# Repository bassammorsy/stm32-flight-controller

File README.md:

# STM32F405 Quadcopter Flight Controller
A custom 4-layer flight controller PCB designed from scratch in KiCad, targeting Betaflight compatibility with 4S–6S LiPo input. Designed, laid out, and submitted for SMT assembly through JLCPCB.

## Specifications
| Parameter | Detail |
|---|---|
| Microcontroller | STM32F405RGTx — ARM Cortex-M4 @ 168 MHz |
| Input Voltage | 4S–6S LiPo (14.8V–25.2V) |
| Power Architecture | TPS54360DDA Buck (5V/3.5A) → SPX3819 LDO (3.3V) |
| IMU | ICM-42688-P (SPI1, 6-DOF, 32kHz ODR) |
| Barometer | BMP388 (SPI3) |
| Magnetometer | QMC5883L (I2C2) |
| GPS | SAM-M10Q-00B (UART3, integrated antenna) |
| OSD | AT7456E with 27MHz crystal |
| USB | USB-C with USBLC6-2SC6 ESD protection |
| PCB | 4-Layer, 74×108mm, FR4 TG135, LeadFree HASL |
| Motor Outputs | 4× DShot (TIM1 CH1-3, TIM8 CH4) |
| Assembly | JLCPCB SMT — 43 component BOM |

## PCB Layout

## Design Portfolio
A full design portfolio documenting every schematic section, PCB layout decision, component selection rationale, and datasheet calculations is available below.

[📄 View Full Design Portfolio (PDF)](Docs/STM32_Drone_FC_Portfolio.pdf)

## Key Design Decisions
- 4-layer stackup: F.Cu (signals) / In1.Cu (GND plane) / In2.Cu (signal overflow) / B.Cu (3.3V distribution)
- Switched node area minimized around TPS54360 to reduce EMI
- Decoupling capacitors placed within 1–2mm of every power pin
- Ground via stitching at all signal layer transitions
- Magnetometer placed at maximum distance from power section
- USBLC6-2SC6 placed immediately at USB-C connector before any D+/D− routing

## Repository Structure

    Hardware/
        Schematic/     — KiCad schematic files
        PCB/           — KiCad PCB layout files
        Gerbers/       — Fabrication files for JLCPCB
    BOM/               — Bill of materials with LCSC part numbers
    Docs/              — Full design portfolio PDF

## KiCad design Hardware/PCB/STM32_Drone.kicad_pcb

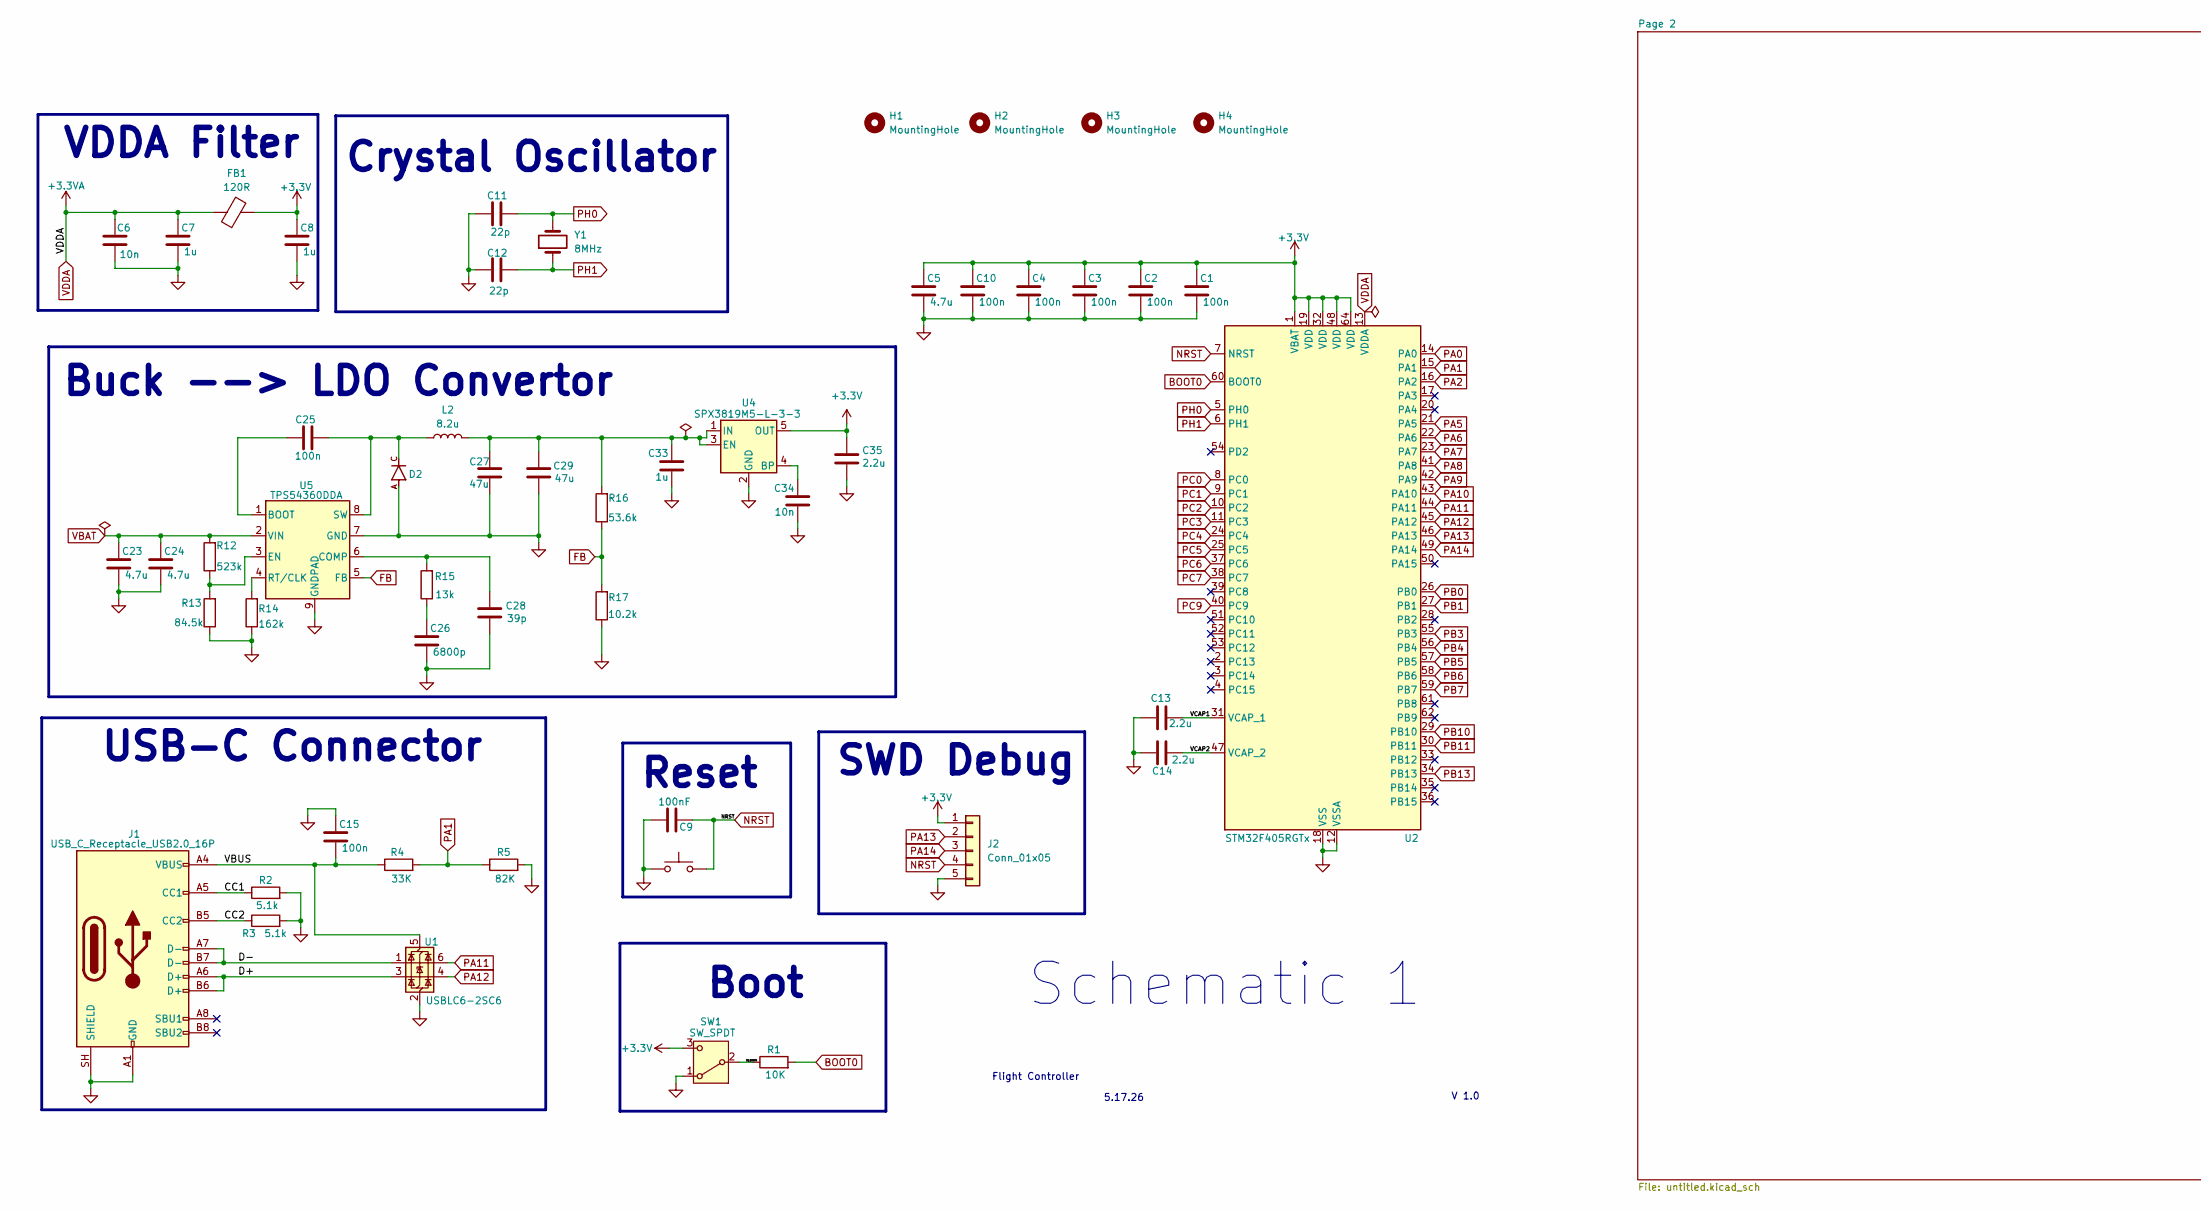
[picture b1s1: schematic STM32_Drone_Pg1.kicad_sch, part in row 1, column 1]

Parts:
C1, C2, C3, C4, C10, C15, C25: 100n; C_0402_1005Metric
C5: 4.7u; C_0805_2012Metric
C6, C34: 10n; C_0402_1005Metric
C7, C8: 1u; C_0805_2012Metric
C9: 100nF; C_0402_1005Metric
C11, C12: 22p; C_0402_1005Metric
C13, C14, C35: 2.2u; C_0402_1005Metric
C23, C24: 4.7u; C_1210_3225Metric
C26: 6800p; C_0402_1005Metric
C27, C29: 47u; C_1210_3225Metric
C28: 39p; C_0402_1005Metric
C33: 1u; C_0402_1005Metric
D2: B560C-13-F; B560C-13F
FB1: 120R; L_0402_1005Metric
H1, H2, H3, H4: MountingHole; MountingHole_3.2mm_M3
J1: USB_C_Receptacle_USB2.0_16P; USB_C_Receptacle_XKB_U262-16XN-4BVC11
J2: Conn_01x05; PinHeader_1x05_P2.54mm_Vertical
L2: 8.2u; L_7.3x7.3_H3.5
R1: 10K; R_0402_1005Metric
R2, R3: 5.1k; R_0402_1005Metric
R4: 33K; R_0402_1005Metric
R5: 82K; R_0402_1005Metric
R12: 523k; R_0402_1005Metric
R13: 84.5k; R_0402_1005Metric
R14: 162k; R_0402_1005Metric
R15: 13k; R_0402_1005Metric
R16: 53.6k; R_0402_1005Metric
R17: 10.2k; R_0402_1005Metric
SW1: SW_SPDT; SW_SPDT_CK_JS102011SAQN
SW2: SW_Push; SW_Push_1P1T_XKB_TS-1187A
U1: USBLC6-2SC6; SOT-23-6
U2: STM32F405RGTx; LQFP-64_10x10mm_P0.5mm
U4: SPX3819M5-L-3-3; SOT-23-5
U5: TPS54360DDA; TI_SO-PowerPAD-8_ThermalVias
Y1: 8MHz; Crystal_SMD_3225-4Pin_3.2x2.5mm

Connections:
+3.3V: C1.2, C2.2, C3.2, C4.2, C5.2, C8.2, C10.2, C35.1, FB1.2, J2.1, SW1.3 (C), U2.1 (VBAT), U2.19 (VDD), U2.32 (VDD), U2.48 (VDD), U2.64 (VDD), U4.5 (OUT); also elsewhere on the board
/CC1: J1.A5 (CC1), R2.1
/CC2: J1.B5 (CC2), R3.1
/D+: J1.A6 (D+), J1.B6 (D+), U1.3 (I/O2)
/D-: J1.A7 (D-), J1.B7 (D-), U1.1 (I/O1)
/SW_BOOT0: R1.1, SW1.2 (B)
/VBUS: C15.1, J1.A4 (VBUS), J1.A9 (VBUS), J1.B4 (VBUS), J1.B9 (VBUS), R4.1, U1.5 (VBUS)
/VCAP1: C13.1, U2.31 (VCAP_1)
/VCAP2: C14.1, U2.47 (VCAP_2)
BOOT0: R1.2, U2.60 (BOOT0)
FB: R16.1, R17.2, U5.5 (FB)
GND: C1.1, C2.1, C3.1, C4.1, C5.1, C6.1, C7.1, C8.1, C9.1, C10.1, C11.2, C12.2, C13.2, C14.2, C15.2, C23.1, C24.1, C26.1, C27.1, C28.1, C29.1, C33.2, C34.2, C35.2, D2.A, J1.A1 (GND), J1.A12 (GND), J1.B1 (GND), J1.B12 (GND), J1.SH (SHIELD), J2.5, R2.2, R3.2, R5.2, R13.1, R14.1, R17.1, SW1.1 (A), SW2.1, U1.2 (GND), U2.12 (VSSA), U2.18 (VSS), U2.63 (VSS), U4.2 (GND), U5.7 (GND), U5.9 (GNDPAD); also elsewhere on the board
NRST: C9.2, J2.4, SW2.2, U2.7 (NRST)
unnamed: C26.2, R15.1
unnamed: C34.1, U4.4 (BP)
unnamed: C27.2, C29.2, C33.1, L2.2, R16.2, U4.1 (IN), U4.3 (EN)
unnamed: C25.2, U5.1 (BOOT)
unnamed: C28.2, R15.2, U5.6 (COMP)
unnamed: R12.1, R13.2, U5.3 (EN)
unnamed: R14.2, U5.4 (RT/CLK)
unnamed: C25.1, D2.C, L2.1, U5.8 (SW)
PA0: U2.14 (PA0); also elsewhere on the board
PA1: R4.2, R5.1, U2.15 (PA1)
PA2: U2.16 (PA2); also elsewhere on the board
PA5: U2.21 (PA5); also elsewhere on the board
PA6: U2.22 (PA6); also elsewhere on the board
PA7: U2.23 (PA7); also elsewhere on the board
PA8: U2.41 (PA8); also elsewhere on the board
PA9: U2.42 (PA9); also elsewhere on the board
PA10: U2.43 (PA10); also elsewhere on the board
PA11: U1.6 (I/O1), U2.44 (PA11)
PA12: U1.4 (I/O2), U2.45 (PA12)
PA13: J2.2, U2.46 (PA13)
PA14: J2.3, U2.49 (PA14)
PB0: U2.26 (PB0); also elsewhere on the board
PB1: U2.27 (PB1); also elsewhere on the board
PB3: U2.55 (PB3); also elsewhere on the board
PB4: U2.56 (PB4); also elsewhere on the board
PB5: U2.57 (PB5); also elsewhere on the board
PB6: U2.58 (PB6); also elsewhere on the board
PB7: U2.59 (PB7); also elsewhere on the board
PB10: U2.29 (PB10); also elsewhere on the board
PB11: U2.30 (PB11); also elsewhere on the board
PB13: U2.34 (PB13); also elsewhere on the board
PC0: U2.8 (PC0); also elsewhere on the board
PC1: U2.9 (PC1); also elsewhere on the board
PC2: U2.10 (PC2); also elsewhere on the board
PC3: U2.11 (PC3); also elsewhere on the board
PC4: U2.24 (PC4); also elsewhere on the board
PC5: U2.25 (PC5); also elsewhere on the board
PC6: U2.37 (PC6); also elsewhere on the board
PC7: U2.38 (PC7); also elsewhere on the board
PC9: U2.40 (PC9); also elsewhere on the board
PH0: C11.1, U2.5 (PH0), Y1.2
PH1: C12.1, U2.6 (PH1), Y1.1
VBAT: C23.2, C24.2, R12.2, U5.2 (VIN); also elsewhere on the board
VDDA: C6.2, C7.2, FB1.1, U2.13 (VDDA)

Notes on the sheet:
V 1.0
SWD Debug
5.17.26
Boot
Reset
Schematic 1
Flight Controller
VDDA Filter
Buck --> LDO Convertor
Crystal Oscillator
USB-C Connector

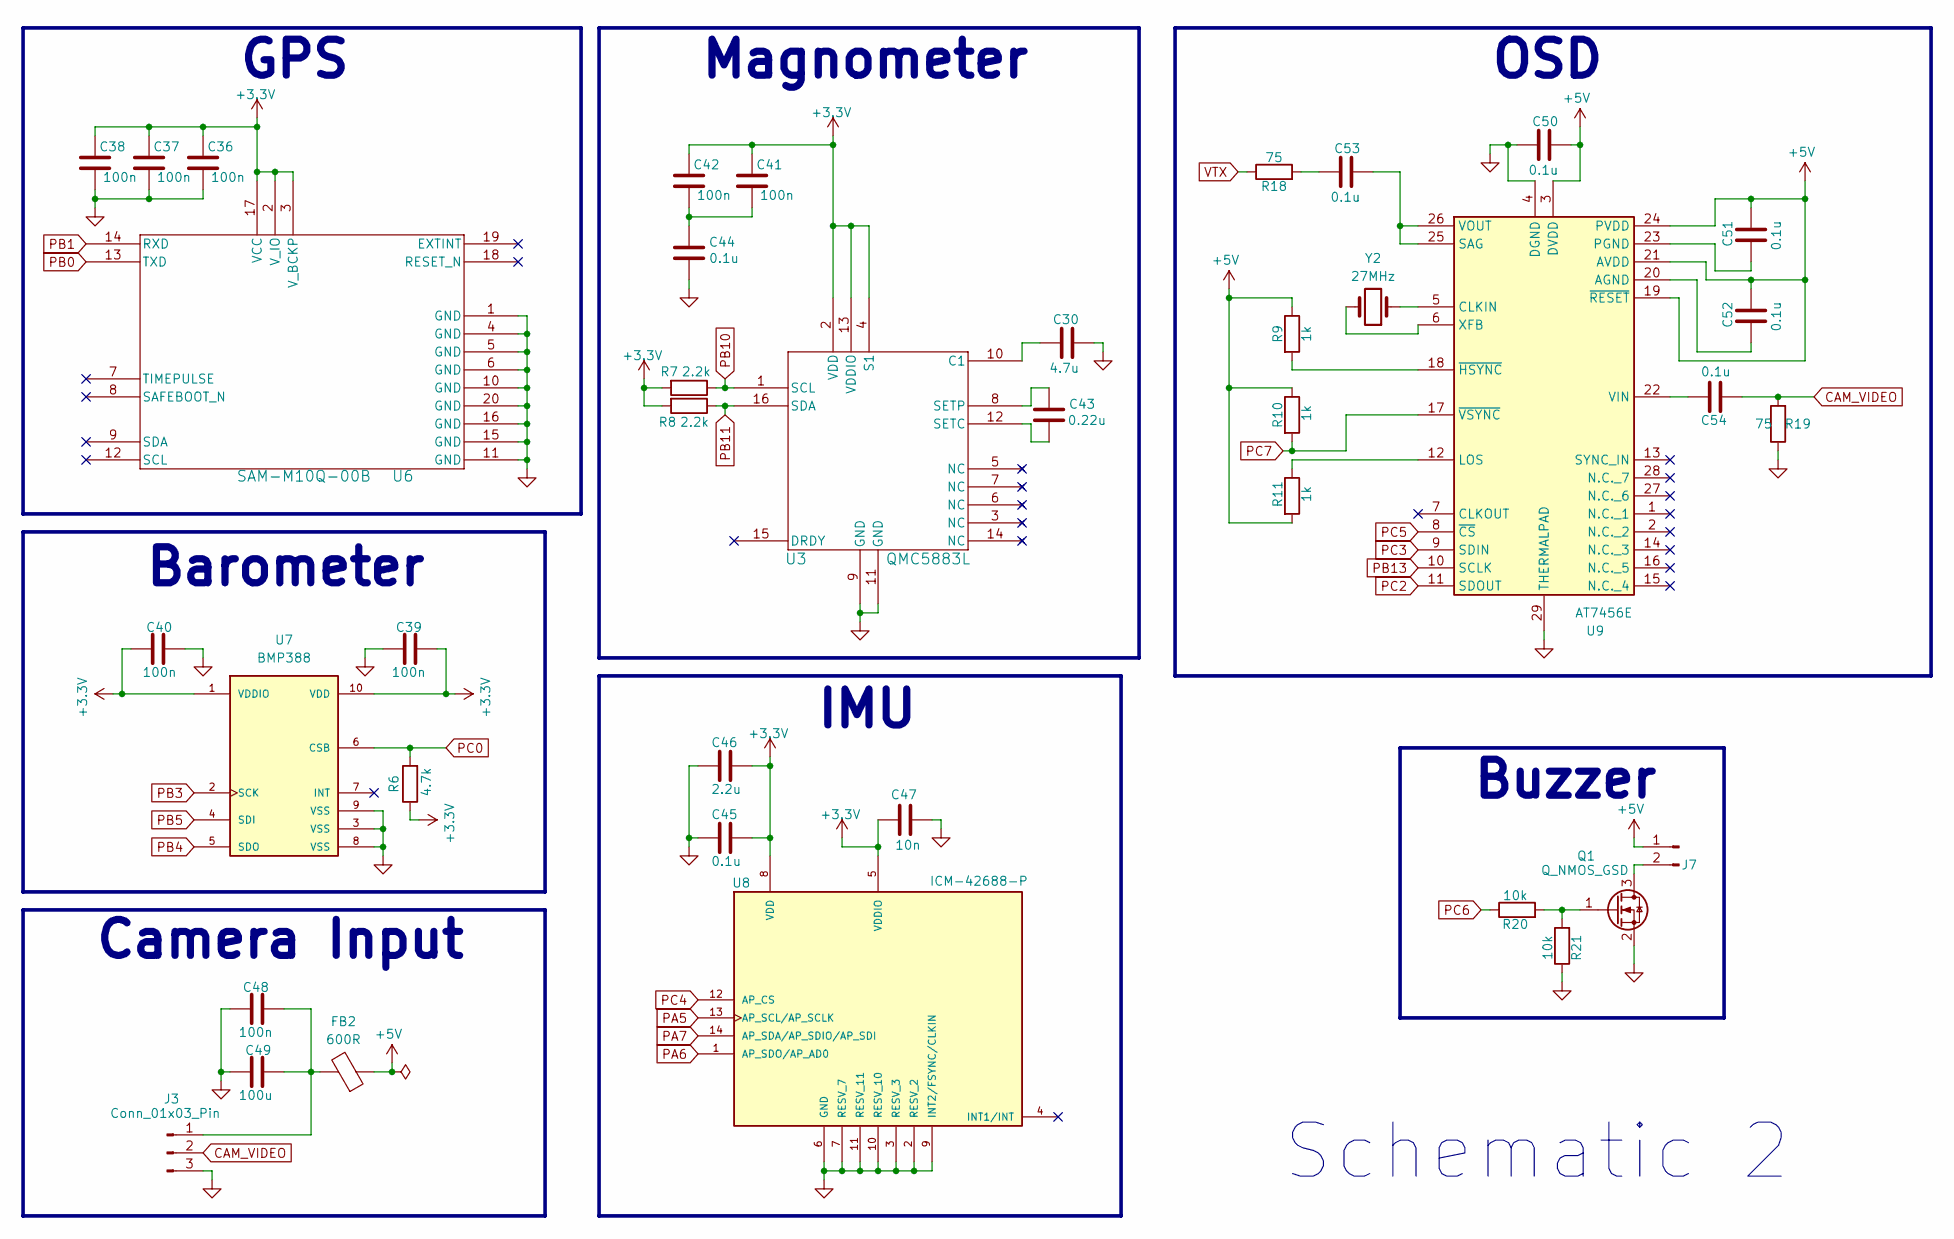
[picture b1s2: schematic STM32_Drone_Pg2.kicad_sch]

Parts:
C30: 4.7u; C_1210_3225Metric
C36, C37, C38, C39, C40, C41, C42, C48: 100n; C_0402_1005Metric
C43: 0.22u; C_0402_1005Metric
C44, C45, C50, C51, C52, C53, C54: 0.1u; C_0402_1005Metric
C46: 2.2u; C_0402_1005Metric
C47: 10n; C_0402_1005Metric
C49: 100u; C_1206_3216Metric
FB2: 600R; L_0402_1005Metric
J3: Conn_01x03_Pin; JST_SH_BM03B-SRSS-TB_1x03-1MP_P1.00mm_Vertical
J7: Conn_01x02_Pin; JST_SH_BM02B-SRSS-TB_1x02-1MP_P1.00mm_Vertical
Q1: Q_NMOS_GSD; SOT-23
R6: 4.7k; R_0402_1005Metric
R7, R8: 2.2k; R_0402_1005Metric
R9, R10, R11: 1k; R_0402_1005Metric
R18, R19: 75; R_0402_1005Metric
R20, R21: 10k; R_0402_1005Metric
U3: QMC5883L; LPCC-16
U6: SAM-M10Q-00B; XCVR_SAM-M10Q-00B
U7: BMP388; XDCR_BMP388; PARTREV 1.7
U8: ICM-42688-P; PQFN50P300X250X97-14N; PARTREV 1.2
U9: AT7456E; SOP65P640X120-29N; Manufacturer_Part_Number AT7456E
Y2: 27MHz; Crystal_SMD_3225-4Pin_3.2x2.5mm

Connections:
+3.3V: C36.2, C37.2, C38.2, C39.1, C40.1, C41.2, C42.2, C45.2, C46.2, C47.2, R6.1, R7.2, R8.2, U3.2 (VDD), U3.4 (S1), U3.13 (VDDIO), U6.2 (V_IO), U6.3 (V_BCKP), U6.17 (VCC), U7.1 (VDDIO), U7.10 (VDD), U8.5 (VDDIO), U8.8 (VDD); also elsewhere on the board
+5V: C50.2, C51.2, C52.2, FB2.1, J7.1, R9.1, R10.1, R11.2, U9.3 (DVDD), U9.19 (~RESET), U9.21 (AVDD), U9.24 (PVDD); also elsewhere on the board
CAM_VIDEO: C54.1, J3.2, R19.2
GND: C30.1, C36.1, C37.1, C38.1, C39.2, C40.2, C44.2, C45.1, C46.1, C47.1, C48.2, C49.2, C50.1, J3.3, Q1.2 (S), R19.1, R21.1, U3.9 (GND), U3.11 (GND), U6.1 (GND), U6.4 (GND), U6.5 (GND), U6.6 (GND), U6.10 (GND), U6.11 (GND), U6.15 (GND), U6.16 (GND), U6.20 (GND), U7.3 (VSS), U7.8 (VSS), U7.9 (VSS), U8.2 (RESV_2), U8.3 (RESV_3), U8.6 (GND), U8.7 (RESV_7), U8.9 (INT2/FSYNC/CLKIN), U8.10 (RESV_10), U8.11 (RESV_11), U9.4 (DGND), U9.29 (THERMALPAD); also elsewhere on the board
unnamed: C41.1, C42.1, C44.1
unnamed: C53.1, R18.2
unnamed: C48.1, C49.1, FB2.2, J3.1
unnamed: J7.2, Q1.3 (D)
unnamed: Q1.1 (G), R20.2, R21.2
unnamed: C30.2, U3.10 (C1)
unnamed: C43.2, U3.12 (SETC)
unnamed: C43.1, U3.8 (SETP)
unnamed: C52.1, U9.20 (AGND)
unnamed: U9.5 (CLKIN), Y2.1
unnamed: R11.1, U9.12 (LOS)
unnamed: C51.1, U9.23 (PGND)
unnamed: C53.2, U9.25 (SAG), U9.26 (VOUT)
unnamed: C54.2, U9.22 (VIN)
unnamed: U9.6 (XFB), Y2.2
unnamed: R9.2, U9.18 (~HSYNC)
PA5: U8.13 (AP_SCL/AP_SCLK); also elsewhere on the board
PA6: U8.1 (AP_SDO/AP_AD0); also elsewhere on the board
PA7: U8.14 (AP_SDA/AP_SDIO/AP_SDI); also elsewhere on the board
PB0: U6.13 (TXD); also elsewhere on the board
PB1: U6.14 (RXD); also elsewhere on the board
PB3: U7.2 (SCK); also elsewhere on the board
PB4: U7.5 (SDO); also elsewhere on the board
PB5: U7.4 (SDI); also elsewhere on the board
PB10: R7.1, U3.1 (SCL); also elsewhere on the board
PB11: R8.1, U3.16 (SDA); also elsewhere on the board
PB13: U9.10 (SCLK); also elsewhere on the board
PC0: R6.2, U7.6 (CSB); also elsewhere on the board
PC2: U9.11 (SDOUT); also elsewhere on the board
PC3: U9.9 (SDIN); also elsewhere on the board
PC4: U8.12 (AP_CS); also elsewhere on the board
PC5: U9.8 (~CS); also elsewhere on the board
PC6: R20.1; also elsewhere on the board
PC7: R10.2, U9.17 (~VSYNC); also elsewhere on the board
VTX: R18.1; also elsewhere on the board

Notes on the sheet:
OSD
Barometer
Schematic 2
Buzzer
Magnometer
IMU
GPS
Camera Input

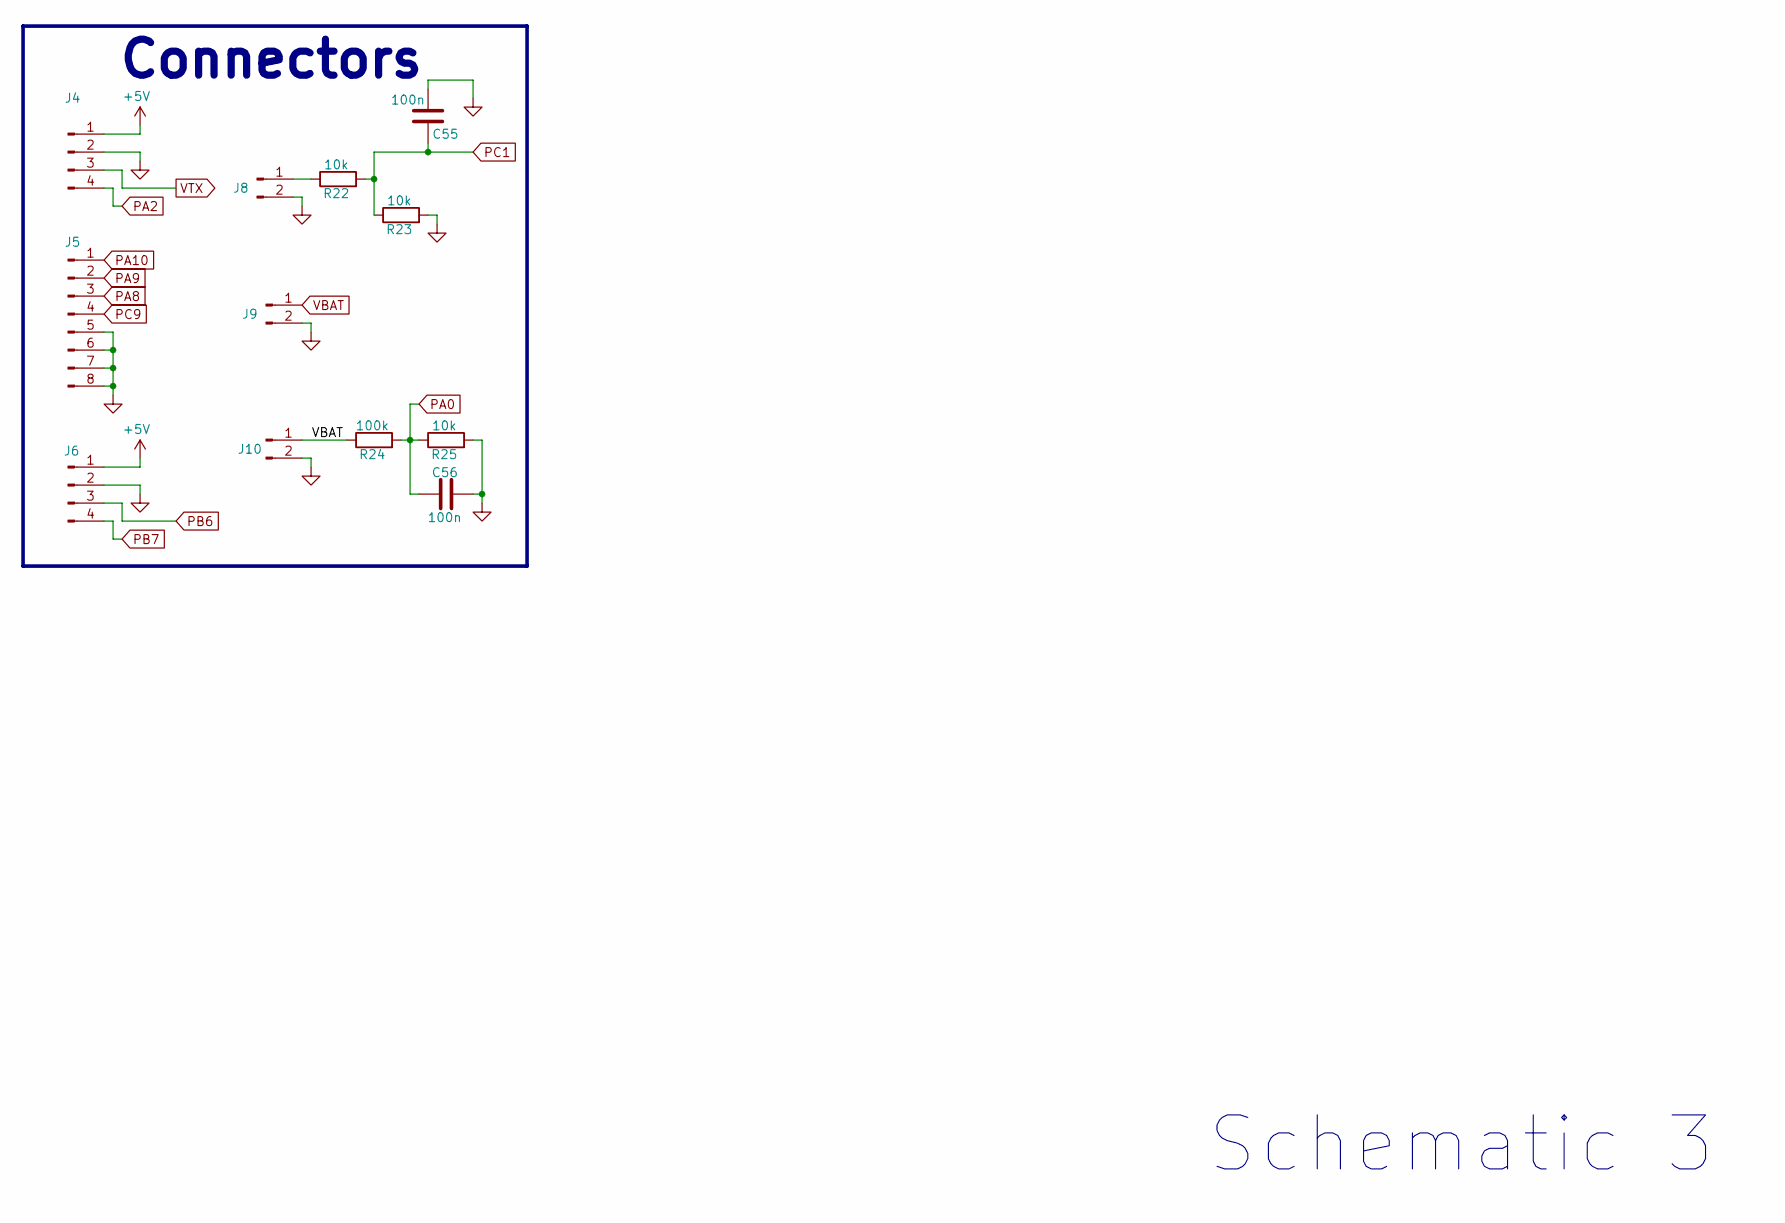
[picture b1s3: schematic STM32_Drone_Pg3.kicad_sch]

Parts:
C55, C56: 100n; C_0402_1005Metric
J4, J6: Conn_01x04_Pin; JST_SH_BM04B-SRSS-TB_1x04-1MP_P1.00mm_Vertical
J5: Conn_01x08_Pin; JST_SH_BM08B-SRSS-TB_1x08-1MP_P1.00mm_Vertical
J8: Conn_01x02_Pin; JST_SH_BM02B-SRSS-TB_1x02-1MP_P1.00mm_Vertical
J9, J10: Conn_01x02_Pin; AMASS_XT30PW-F_1x02_P2.50mm_Horizontal
R22, R23, R25: 10k; R_0402_1005Metric
R24: 100k; R_0402_1005Metric

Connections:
+5V: J4.1, J6.1; also elsewhere on the board
GND: C55.2, C56.1, J4.2, J5.5, J5.6, J5.7, J5.8, J6.2, J8.2, J9.2, J10.2, R23.2, R25.2; also elsewhere on the board
unnamed: J8.1, R22.1
PA0: C56.2, R24.2, R25.1; also elsewhere on the board
PA2: J4.4; also elsewhere on the board
PA8: J5.3; also elsewhere on the board
PA9: J5.2; also elsewhere on the board
PA10: J5.1; also elsewhere on the board
PB6: J6.3; also elsewhere on the board
PB7: J6.4; also elsewhere on the board
PC1: C55.1, R22.2, R23.1; also elsewhere on the board
PC9: J5.4; also elsewhere on the board
VBAT: J9.1, J10.1, R24.1; also elsewhere on the board
VTX: J4.3; also elsewhere on the board

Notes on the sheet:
Connectors
Schematic 3

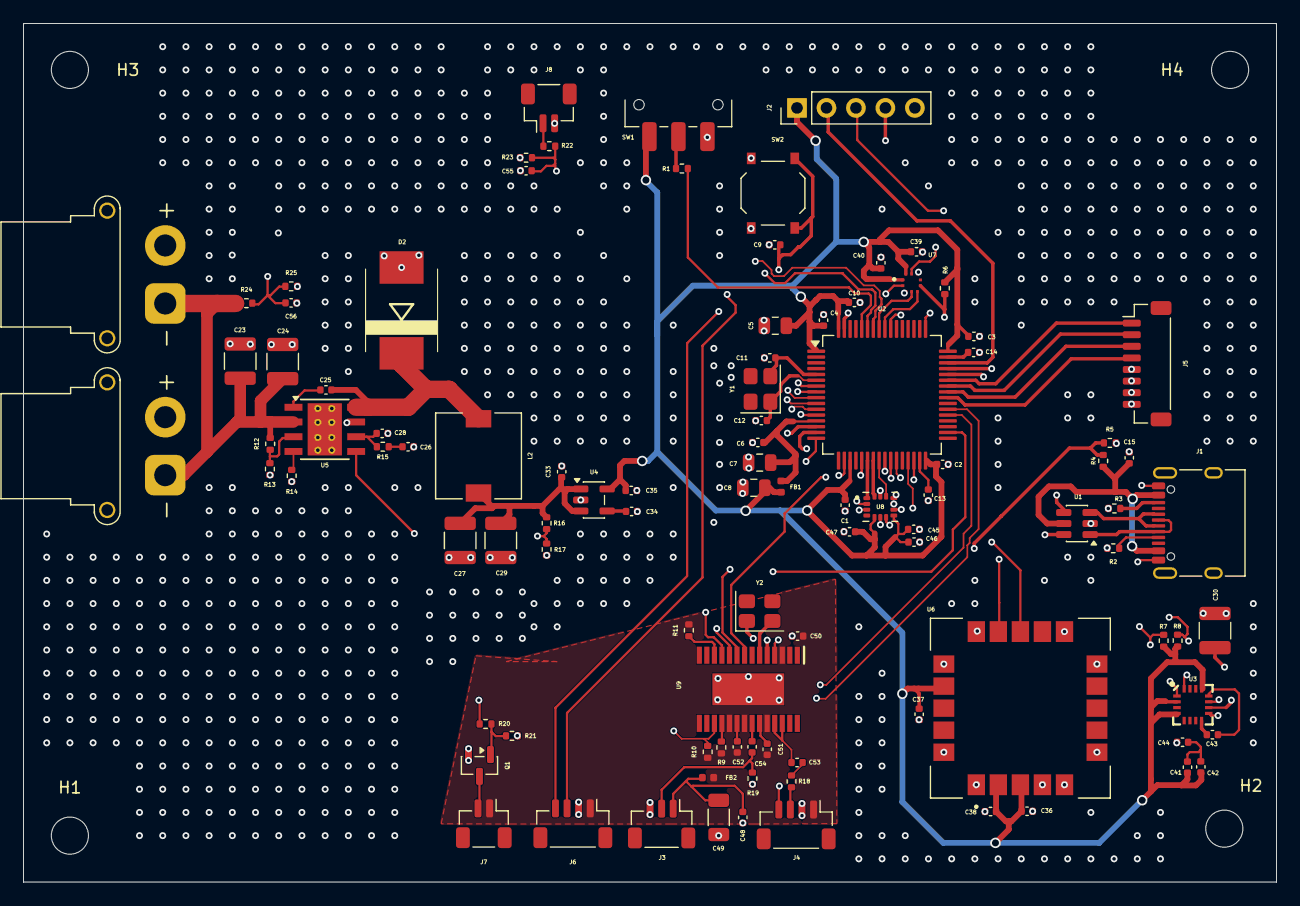
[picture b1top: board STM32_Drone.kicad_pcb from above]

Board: 4 copper layers, 108.0 x 74.0 mm, 104 parts (0 on the bottom side), 77 nets.

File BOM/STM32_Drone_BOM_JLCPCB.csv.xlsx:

Reference | Qty | Value | Footprint | LCSC Part #
C1,C2,C3,C4,C10,C15,C25,C36,C37,C38,C39,C40,C41,C42,C48,C55,C56 | 17 | 100n | Capacitor_SMD:C_0402_1005Metric | C1525
C5 | 1 | 4.7u | Capacitor_SMD:C_0805_2012Metric | C1779
C6,C34,C47 | 3 | 10n | Capacitor_SMD:C_0402_1005Metric | C15195
C7,C8 | 2 | 1u | Capacitor_SMD:C_0805_2012Metric | C28323
C9 | 1 | 100nF | Capacitor_SMD:C_0402_1005Metric | C1525
C11,C12 | 2 | 22p | Capacitor_SMD:C_0402_1005Metric | C1555
C13,C14,C35,C46 | 4 | 2.2u | Capacitor_SMD:C_0402_1005Metric | C12530
C23,C24,C30 | 3 | 4.7u | Capacitor_SMD:C_1210_3225Metric | C23733
C26 | 1 | 6800p | Capacitor_SMD:C_0402_1005Metric | C93654
C27,C29 | 2 | 47u | Capacitor_SMD:C_1210_3225Metric | C77101
C28 | 1 | 39p | Capacitor_SMD:C_0402_1005Metric | C106223
C33 | 1 | 1u | Capacitor_SMD:C_0402_1005Metric | C52923
C43 | 1 | 0.22u | Capacitor_SMD:C_0402_1005Metric | C16772
C44,C45,C50,C51,C52,C53,C54 | 7 | 0.1u | Capacitor_SMD:C_0402_1005Metric | C1525
C49 | 1 | 100u | Capacitor_SMD:C_1206_3216Metric | C15008
D2 | 1 | B560C-13-F | Custom:B560C-13F | C85100
FB1 | 1 | 120R | Inductor_SMD:L_0402_1005Metric | C38480
FB2 | 1 | 600R | Inductor_SMD:L_0402_1005Metric | C76884
R1 | 1 | 10K | Resistor_SMD:R_0402_1005Metric | C25744
R2,R3 | 2 | 5.1k | Resistor_SMD:R_0402_1005Metric | C25905
R4 | 1 | 33K | Resistor_SMD:R_0402_1005Metric | C25779
R5 | 1 | 82K | Resistor_SMD:R_0402_1005Metric | C1160
R6 | 1 | 4.7k | Resistor_SMD:R_0402_1005Metric | C25900
R7,R8 | 2 | 2.2k | Resistor_SMD:R_0402_1005Metric | C25879
R9,R10,R11 | 3 | 1k | Resistor_SMD:R_0402_1005Metric | C11702
R12 | 1 | 523k | Resistor_SMD:R_0402_1005Metric | C27011
R13 | 1 | 84.5k | Resistor_SMD:R_0402_1005Metric | C26988
R14 | 1 | 162k | Resistor_SMD:R_0402_1005Metric | C54068
R15 | 1 | 13k | Resistor_SMD:R_0402_1005Metric | C25754
R16 | 1 | 53.6k | Resistor_SMD:R_0402_1005Metric | C53398
R17 | 1 | 10.2k | Resistor_SMD:R_0402_1005Metric | C11660
R18,R19 | 2 | 75 | Resistor_SMD:R_0402_1005Metric | C25133
R20,R21,R22,R23,R25 | 5 | 10k | Resistor_SMD:R_0402_1005Metric | C25744
R24 | 1 | 100k | Resistor_SMD:R_0402_1005Metric | C25741
U1 | 1 | USBLC6-2SC6 | Package_TO_SOT_SMD:SOT-23-6 | C7519
U2 | 1 | STM32F405RGTx | Package_QFP:LQFP-64_10x10mm_P0.5mm | C15742
U3 | 1 | QMC5883L | Custom:LPCC-16 | C976032
U4 | 1 | SPX3819M5-L-3-3 | Package_TO_SOT_SMD:SOT-23-5 | C9055
U5 | 1 | TPS54360DDA | Package_SO:TI_SO-PowerPAD-8_ThermalVias | C465733
U6 | 1 | SAM-M10Q-00B | Custom:XCVR_SAM-M10Q-00B | C5443880
U7 | 1 | BMP388 | Custom:XDCR_BMP388 | C779278
U8 | 1 | ICM-42688-P | Custom:PQFN50P300X250X97-14N | C1850418
U9 | 1 | AT7456E | Custom:SOP65P640X120-29N | C82351

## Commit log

2026-06-04 Revise README
    Updated README to enhance clarity and detail about the STM32F405 quadcopter flight controller, including specifications, repository structure, design portfolio, and key design decisions.
2026-06-04 files
2026-06-04 BOM files added
2026-06-04 Portfolio added
2026-06-04 Added hardware folder
2026-06-04 Datasheets added
2026-06-04 Updated README
    Updated the design portfolio description and added a link to the PDF.
2026-06-04 Added images folder
